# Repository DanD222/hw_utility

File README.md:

# PCB design for utility module
Utility hardware design for Audio Module, Analog Inputs, I2C/SPI sensors, RS232 and some digitial inputs. 
- PCB assembly files are below pcb/assembly/
- PDF Schematic is below pcb/pdf_exports/ 

## Components
- STM32F103 Bluepill board.
- 9 to 30V DC DC power supply.
- PAM8302AAS  audio amplifier connected to STM32F1 PWM output
- Screwterminal for loudspeaker
- RJ45 connector for sensing e.g. gear, flaps, airbrakes postion
- RJ45 connector for CAN Interface and CAN transceiver
- RJ12 connector with analog and digital inputs
- 1.27mm pitch header for external I2C devices
- 1.27mm pitch header for RS232 and SPI interface

## Pictures

## Improvements for next version
- External connectors for voltage / I2C / RS232 are tiny.  Increase size to e.g. 2.54mm pitch or chose a different connector.
- Make external i2c sensor voltage switchable to be able to perform a hard sensor reset. 
- Replace C32 47uF with a sufficient voltage rating. The used one is only specified for up to 10V!

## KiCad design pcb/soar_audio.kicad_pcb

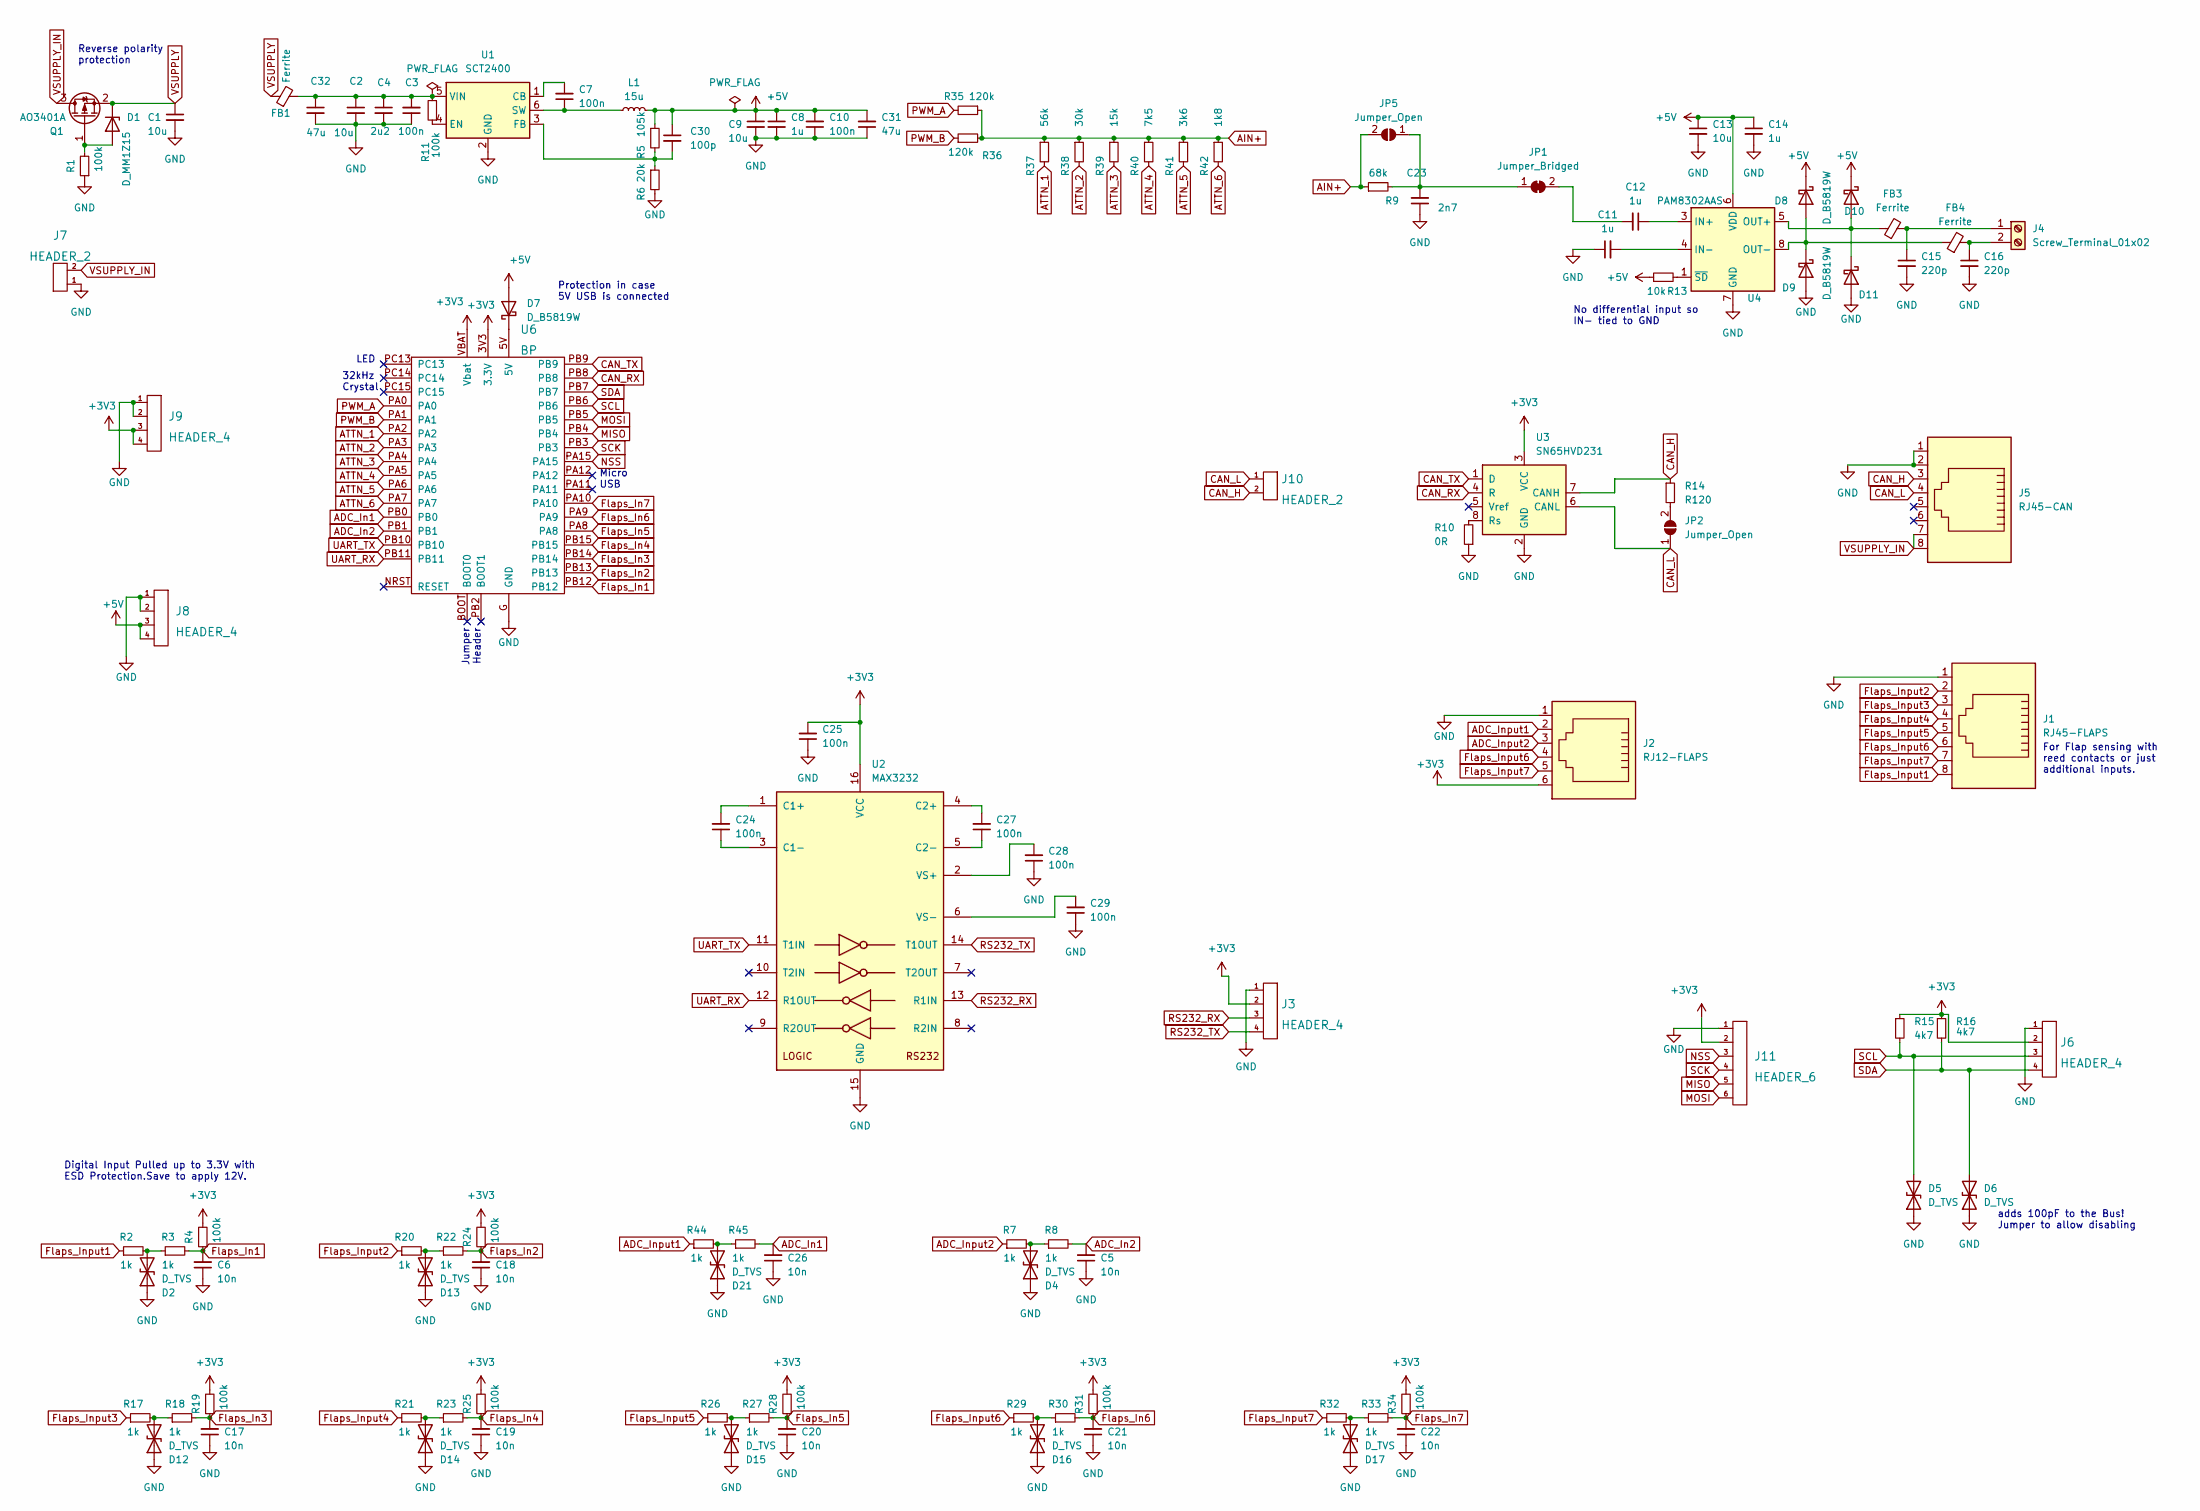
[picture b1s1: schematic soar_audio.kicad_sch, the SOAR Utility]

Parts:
C1, C2, C9: 10u; C_0805_2012Metric; LCSC C440198
C3, C7, C10, C24, C25, C27, C28, C29: 100n; C_0603_1608Metric; LCSC C14663
C4: 2u2; C_0805_2012Metric; LCSC C49217
C5, C6, C17, C18, C19, C20, C21, C22, C26: 10n; C_0603_1608Metric; LCSC C57112
C8, C11, C12, C14: 1u; C_0603_1608Metric; LCSC C15849
C13: 10u; C_0603_1608Metric; LCSC C19702
C15, C16: 220p; C_0603_1608Metric; LCSC C1603
C23: 2n7; C_0603_1608Metric; LCSC C1609
C30: 100p; C_0603_1608Metric; LCSC C14858
C31, C32: 47u; C_1206_3216Metric; LCSC C96123
D1: D_MM1Z15; D_SOD-123; LCSC C86235
D2, D4, D5, D6, D12, D13, D14, D15, D16, D17, D21: D_TVS; D_SOD-323; LCSC C51450
D7, D8, D9, D10, D11: D_B5819W; D_SOD-123; LCSC C8598
FB1, FB3, FB4: Ferrite; L_0805_2012Metric; LCSC C1017
J1: RJ45-FLAPS; RJ45_Amphenol_RJHSE5380
J2: RJ12-FLAPS; RJ12_Amphenol_54601
J3, J6: HEADER_4; PinHeader_1x04_P1.27mm_Vertical
J4: Screw_Terminal_01x02; TerminalBlock_bornier-2_P5.08mm
J5: RJ45-CAN; RJ45_Amphenol_RJHSE5380
J7, J10: HEADER_2; PinHeader_1x02_P1.27mm_Vertical
J8, J9: HEADER_4; PinHeader_1x04_P2.54mm_Vertical
J11: HEADER_6; PinHeader_1x06_P1.27mm_Vertical
JP1: Jumper_Bridged; SolderJumper-2_P1.3mm_Bridged_Pad1.0x1.5mm
JP2, JP5: Jumper_Open; SolderJumper-2_P1.3mm_Open_Pad1.0x1.5mm
L1: 15u; SLO0630H; LCSC C182182
Q1: AO3401A; SOT-23; LCSC C15127
R1, R4, R11, R19, R24, R25, R28, R31, R34: 100k; R_0603_1608Metric; LCSC C25803
R2, R7, R17, R20, R21, R26, R29, R32, R44: 1k; R_0805_2012Metric; LCSC C17513
R3, R8, R18, R22, R23, R27, R30, R33, R45: 1k; R_0603_1608Metric; LCSC C21190
R5: 105k; R_0603_1608Metric; LCSC C16840
R6: 20k; R_0603_1608Metric; LCSC C4184
R9: 68k; R_0603_1608Metric; LCSC C23231
R10: 0R; R_0603_1608Metric; LCSC C21189
R13: 10k; R_0603_1608Metric; LCSC C25804
R14: R120; R_0603_1608Metric; LCSC C22787
R15, R16: 4k7; R_0603_1608Metric; LCSC C23162
R35, R36: 120k; R_0603_1608Metric; LCSC C25808
R37: 56k; R_0603_1608Metric; LCSC C23206
R38: 30k; R_0603_1608Metric; LCSC C22984
R39: 15k; R_0603_1608Metric; LCSC C22809
R40: 7k5; R_0603_1608Metric; LCSC C23234
R41: 3k6; R_0603_1608Metric; LCSC C22980
R42: 1k8; R_0603_1608Metric; LCSC C4177
U1: SCT2400; TSOT-23-6; LCSC C2693819
U2: MAX3232; HTSSOP-16-1EP_4.4x5mm_P0.65mm_EP3x3mm; LCSC C11317
U3: SN65HVD231; SOIC-8_3.9x4.9mm_P1.27mm; LCSC C129257
U4: PAM8302AAS; MSOP-8_3x3mm_P0.65mm; LCSC C113367
U6: BP; blue_pill

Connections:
+3V3: C25.2, J2.6, J3.2, J6.2, J9.3, J9.4, J11.2, R4.2, R15.1, R16.1, R19.2, R24.2, R25.2, R28.2, R31.2, R34.2, U2.16 (VCC), U3.3 (VCC), U6.3V3 (3.3V), U6.VBAT (Vbat)
+5V: C8.1, C9.1, C10.2, C13.1, C14.1, C30.1, C31.2, D7.2 (A), D8.1 (K), D10.1 (K), J8.3, J8.4, L1.2, R5.1, R13.1, U4.6 (VDD)
ADC_In1: C26.2, R45.2, U6.PB0
ADC_In2: C5.2, R8.2, U6.PB1
ADC_Input1: J2.2, R44.1
ADC_Input2: J2.3, R7.1
AIN+: JP5.2 (B), R9.1, R35.1, R36.2, R37.1, R38.1, R39.1, R40.1, R41.1, R42.1
ATTN_1: R37.2, U6.PA2
ATTN_2: R38.2, U6.PA3
ATTN_3: R39.2, U6.PA4
ATTN_4: R40.2, U6.PA5
ATTN_5: R41.2, U6.PA6
ATTN_6: R42.2, U6.PA7
CAN_H: J5.3, J10.2, R14.1, U3.7 (CANH)
CAN_L: J5.4, J10.1, JP2.1 (A), U3.6 (CANL)
CAN_RX: U3.4 (R), U6.PB8
CAN_TX: U3.1 (D), U6.PB9
Flaps_In1: C6.2, R3.2, R4.1, U6.PB12
Flaps_In2: C18.2, R22.2, R24.1, U6.PB13
Flaps_In3: C17.2, R18.2, R19.1, U6.PB14
Flaps_In4: C19.2, R23.2, R25.1, U6.PB15
Flaps_In5: C20.2, R27.2, R28.1, U6.PA8
Flaps_In6: C21.2, R30.2, R31.1, U6.PA9
Flaps_In7: C22.2, R33.2, R34.1, U6.PA10
Flaps_Input1: J1.8, R2.1
Flaps_Input2: J1.2, R20.1
Flaps_Input3: J1.3, R17.1
Flaps_Input4: J1.4, R21.1
Flaps_Input5: J1.5, R26.1
Flaps_Input6: J1.6, J2.4, R29.1
Flaps_Input7: J1.7, J2.5, R32.1
GND: C1.2, C2.2, C3.1, C4.2, C5.1, C6.1, C8.2, C9.2, C10.1, C11.1, C13.2, C14.2, C15.2, C16.2, C17.1, C18.1, C19.1, C20.1, C21.1, C22.1, C23.1, C25.1, C26.1, C28.1, C29.1, C31.1, C32.2, D2.1 (A1), D4.1 (A1), D5.1 (A1), D6.1 (A1), D9.2 (A), D11.2 (A), D12.1 (A1), D13.1 (A1), D14.1 (A1), D15.1 (A1), D16.1 (A1), D17.1 (A1), D21.1 (A1), J1.1, J2.1, J3.1, J5.1, J5.2, J6.1, J7.1, J8.1, J8.2, J9.1, J9.2, J11.1, R1.1, R6.2, R10.1, U1.2 (GND), U2.15 (GND), U3.2 (GND), U4.7 (GND), U6.G (GND)
MISO: J11.5, U6.PB4
MOSI: J11.6, U6.PB5
NSS: J11.3, U6.PA15
unnamed: C2.1, C3.2, C4.1, C32.1, FB1.2, R11.2, U1.5 (VIN)
unnamed: C7.1, L1.1, U1.6 (SW)
unnamed: C7.2, U1.1 (CB)
unnamed: C11.2, U4.4 (IN-)
unnamed: C12.1, U4.3 (IN+)
unnamed: C12.2, JP1.2 (B)
unnamed: C15.1, FB3.2, J4.1
unnamed: C16.1, FB4.2, J4.2
unnamed: C23.2, JP1.1 (A), JP5.1 (A), R9.2
unnamed: C24.1, U2.3 (C1-)
unnamed: C24.2, U2.1 (C1+)
unnamed: C27.1, U2.5 (C2-)
unnamed: C27.2, U2.4 (C2+)
unnamed: C28.2, U2.2 (VS+)
unnamed: C29.2, U2.6 (VS-)
unnamed: D1.2 (A), Q1.1 (G), R1.2
unnamed: D2.2 (A2), R2.2, R3.1
unnamed: D4.2 (A2), R7.2, R8.1
unnamed: D7.1 (K), U6.5V
unnamed: D8.2 (A), D9.1 (K), FB4.1, U4.8 (OUT-)
unnamed: D10.2 (A), D11.1 (K), FB3.1, U4.5 (OUT+)
unnamed: D12.2 (A2), R17.2, R18.1
unnamed: D13.2 (A2), R20.2, R22.1
unnamed: D14.2 (A2), R21.2, R23.1
unnamed: D15.2 (A2), R26.2, R27.1
unnamed: D16.2 (A2), R29.2, R30.1
unnamed: D17.2 (A2), R32.2, R33.1
unnamed: D21.2 (A2), R44.2, R45.1
unnamed: JP2.2 (B), R14.2
unnamed: C30.2, R5.2, R6.1, U1.3 (FB)
unnamed: R10.2, U3.8 (Rs)
unnamed: R13.2, U4.1 (~SD)
unnamed: R11.1, U1.4 (EN)
PWM_A: R35.2, U6.PA0
PWM_B: R36.1, U6.PA1
RS232_RX: J3.3, U2.13 (R1IN)
RS232_TX: J3.4, U2.14 (T1OUT)
SCK: J11.4, U6.PB3
SCL: D5.2 (A2), J6.3, R15.2, U6.PB6
SDA: D6.2 (A2), J6.4, R16.2, U6.PB7
UART_RX: U2.12 (R1OUT), U6.PB11
UART_TX: U2.11 (T1IN), U6.PB10
VSUPPLY: C1.1, D1.1 (K), FB1.1, Q1.2 (S)
VSUPPLY_IN: J5.7, J5.8, J7.2, Q1.3 (D)

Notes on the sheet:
Protection in case 5V USB is connected
Micro USB
32kHz Crystal
adds 100pF to the Bus! Jumper to allow disabling
Jumper Header
Reverse polarity protection
No differential input so IN- tied to GND
Digital Input Pulled up to 3.3V with ESD Protection.Save to apply 12V.
For Flap sensing with reed contacts or just additional inputs.
LED

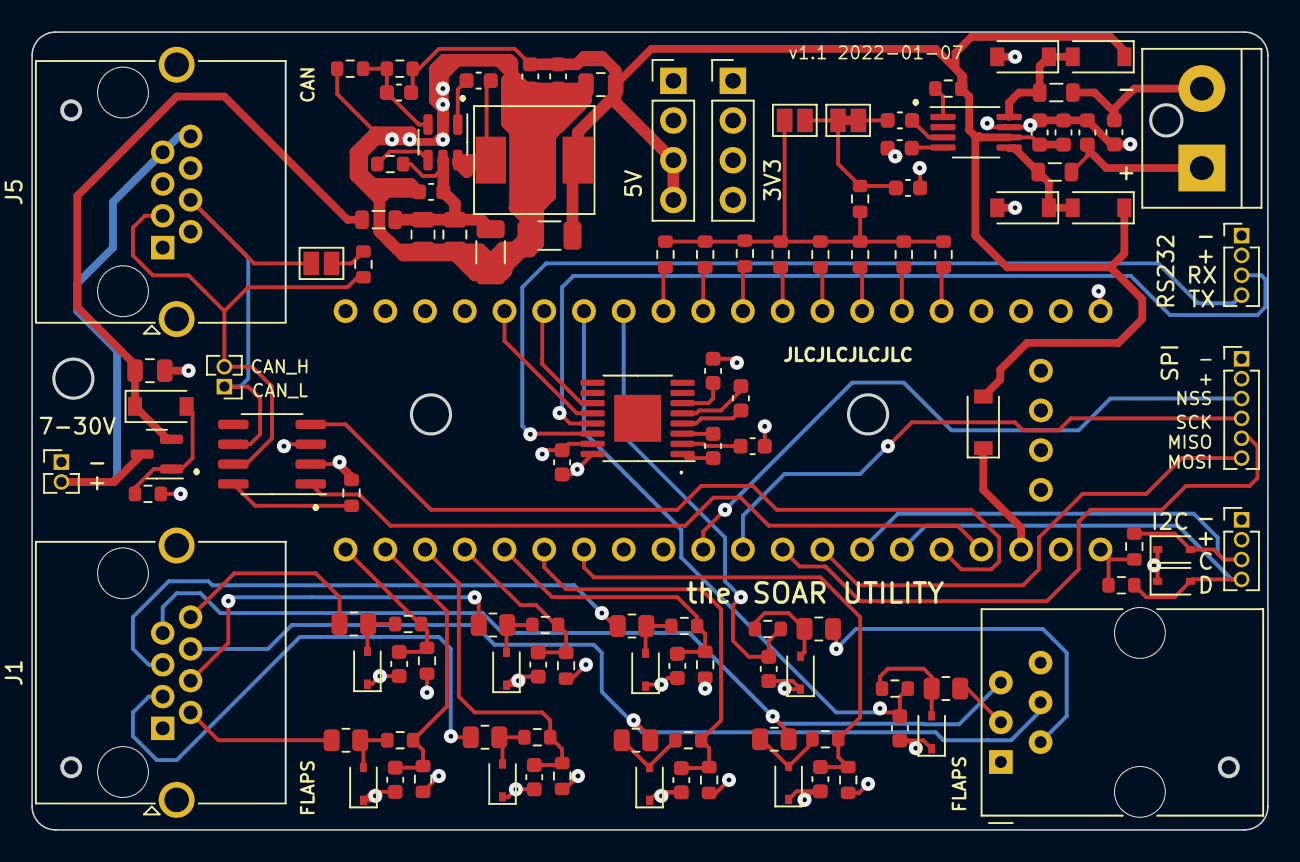
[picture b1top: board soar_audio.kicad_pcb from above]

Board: 4 copper layers, 78.9 x 50.9 mm, 116 parts (0 on the bottom side), 79 nets.

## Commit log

2022-01-02 initial creation
2022-01-02 removed
2022-01-03 started creating pcb
2022-01-03 added dcdc power supply
2022-01-03 added 3v3 power supply
2022-01-04 updated with bluepill and discovery board footprint
2022-01-04 updated schematic and layout
2022-01-04 updated jlc rules to layout
2022-01-04 some more steps done
2022-01-05 add toolingholes
2022-01-05 finalized pcb
2022-01-05 generated gerber files
2022-01-05 generated all assembly files
2022-01-05 replaced out of stock inductor
2022-01-05 add footprint for L
2022-01-05 corrected footprint position file
2022-01-05 some minor changes
2022-01-06 updates based on feedback from Klaus
2022-01-06 finalized pcb and generated v1.0 production files
2022-01-06 corrected part roations
2022-01-06 final ordered version 1.0
2022-01-06 updated description
2022-01-07 changed dc-dc converter
2022-01-07 updated documentation
2022-01-19 added real picture
2022-01-24 added improvement for next version iteration
2022-01-29 hint for next version
2022-02-12 a new todo
2023-08-30 added license
